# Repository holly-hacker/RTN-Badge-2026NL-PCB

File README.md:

# RTN Badge 2026 (NL edition) PCB

This repo contains the KiCAD schematic for the 2026 RTN Badge (NL edition).

For more info, see the [main repo](https://github.com/holly-hacker/RTN-Badge-2026NL).

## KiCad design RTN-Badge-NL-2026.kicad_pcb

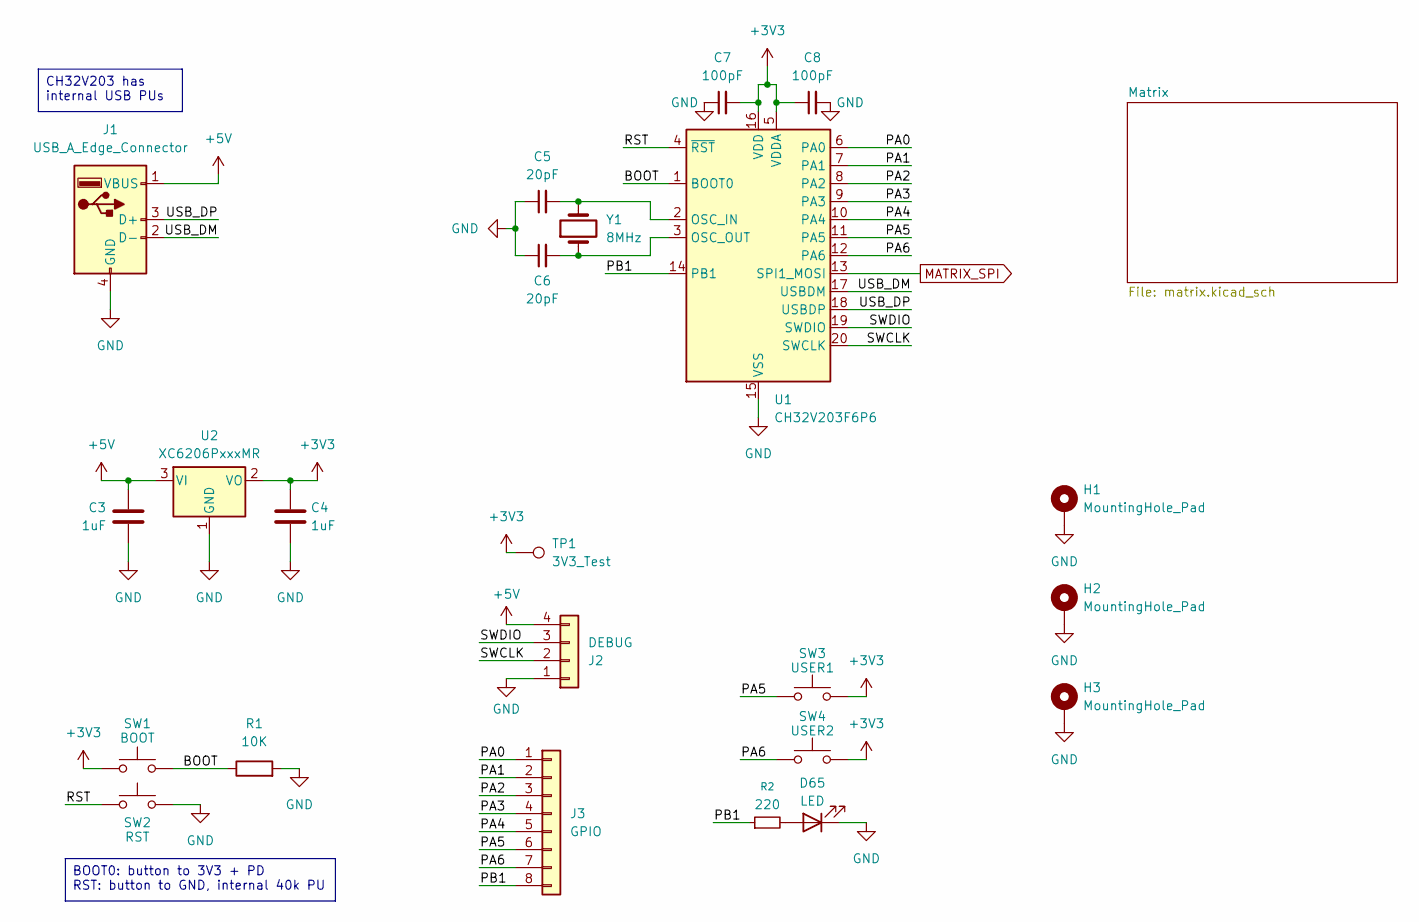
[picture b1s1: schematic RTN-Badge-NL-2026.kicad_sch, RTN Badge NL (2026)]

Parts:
C3, C4: 1uF; C_0603_1608Metric
C5, C6: 20pF; C_0603_1608Metric
C7, C8: 100pF; C_0603_1608Metric
D65: LED; LED_0603_1608Metric
H1, H2, H3: MountingHole_Pad; MountingHole_2.2mm_M2_Pad_Via
J1: USB_A_Edge_Connector; USB_A_PCB_Edge_receptacle
J2: DEBUG; PinSocket_1x04_P2.54mm_Vertical
J3: GPIO; PinSocket_1x08_P2.54mm_Vertical
R1: 10K; R_0603_1608Metric
R2: 220; R_0603_1608Metric
SW1: BOOT; SW_SPST_TS-1088-xR020
SW2: RST; SW_SPST_TS-1088-xR020
SW3: USER1; SW_SPST_TS-1088-xR020
SW4: USER2; SW_SPST_TS-1088-xR020
TP1: 3V3_Test; TestPoint_Pad_D1.0mm
U1: CH32V203F6P6; TSSOP-20_4.4x6.5mm_P0.65mm
U2: XC6206PxxxMR; SOT-23-3
Y1: 8MHz; Crystal_SMD_5032-2Pin_5.0x3.2mm

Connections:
+3V3: C4.1, C7.2, C8.1, SW1.1, SW3.2, SW4.2, TP1.1 (1_1), U1.5 (VDDA), U1.16 (VDD), U2.2 (VO)
+5V: C3.1, J1.1 (VBUS), J2.4, U2.3 (VI); also elsewhere on the board
/BOOT: R1.1, SW1.2, U1.1 (BOOT0)
/PA0: J3.1, U1.6 (PA0)
/PA1: J3.2, U1.7 (PA1)
/PA2: J3.3, U1.8 (PA2)
/PA3: J3.4, U1.9 (PA3)
/PA4: J3.5, U1.10 (PA4)
/PA5: J3.6, SW3.1, U1.11 (PA5)
/PA6: J3.7, SW4.1, U1.12 (PA6)
/PB1: J3.8, R2.1, U1.14 (PB1)
/RST: SW2.1, U1.4 (~RST)
/SWCLK: J2.2, U1.20 (SWCLK)
/SWDIO: J2.3, U1.19 (SWDIO)
/USB_DM: J1.2 (D-), U1.17 (USBDM)
/USB_DP: J1.3 (D+), U1.18 (USBDP)
GND: C3.2, C4.2, C5.1, C6.1, C7.1, C8.2, D65.1 (K), H1.1 (1_1), H2.1 (1_1), H3.1 (1_1), J1.4 (GND), J2.1, R1.2, SW2.2, U1.15 (VSS), U2.1 (GND); also elsewhere on the board
MATRIX_SPI: U1.13 (SPI1_MOSI); also elsewhere on the board
unnamed: D65.2 (A), R2.2
unnamed: C5.2, U1.2 (OSC_IN), Y1.2
unnamed: C6.2, U1.3 (OSC_OUT), Y1.1

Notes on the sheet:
CH32V203 has internal USB PUs
BOOT0: button to 3V3 + PD RST: button to GND, internal 40k PU

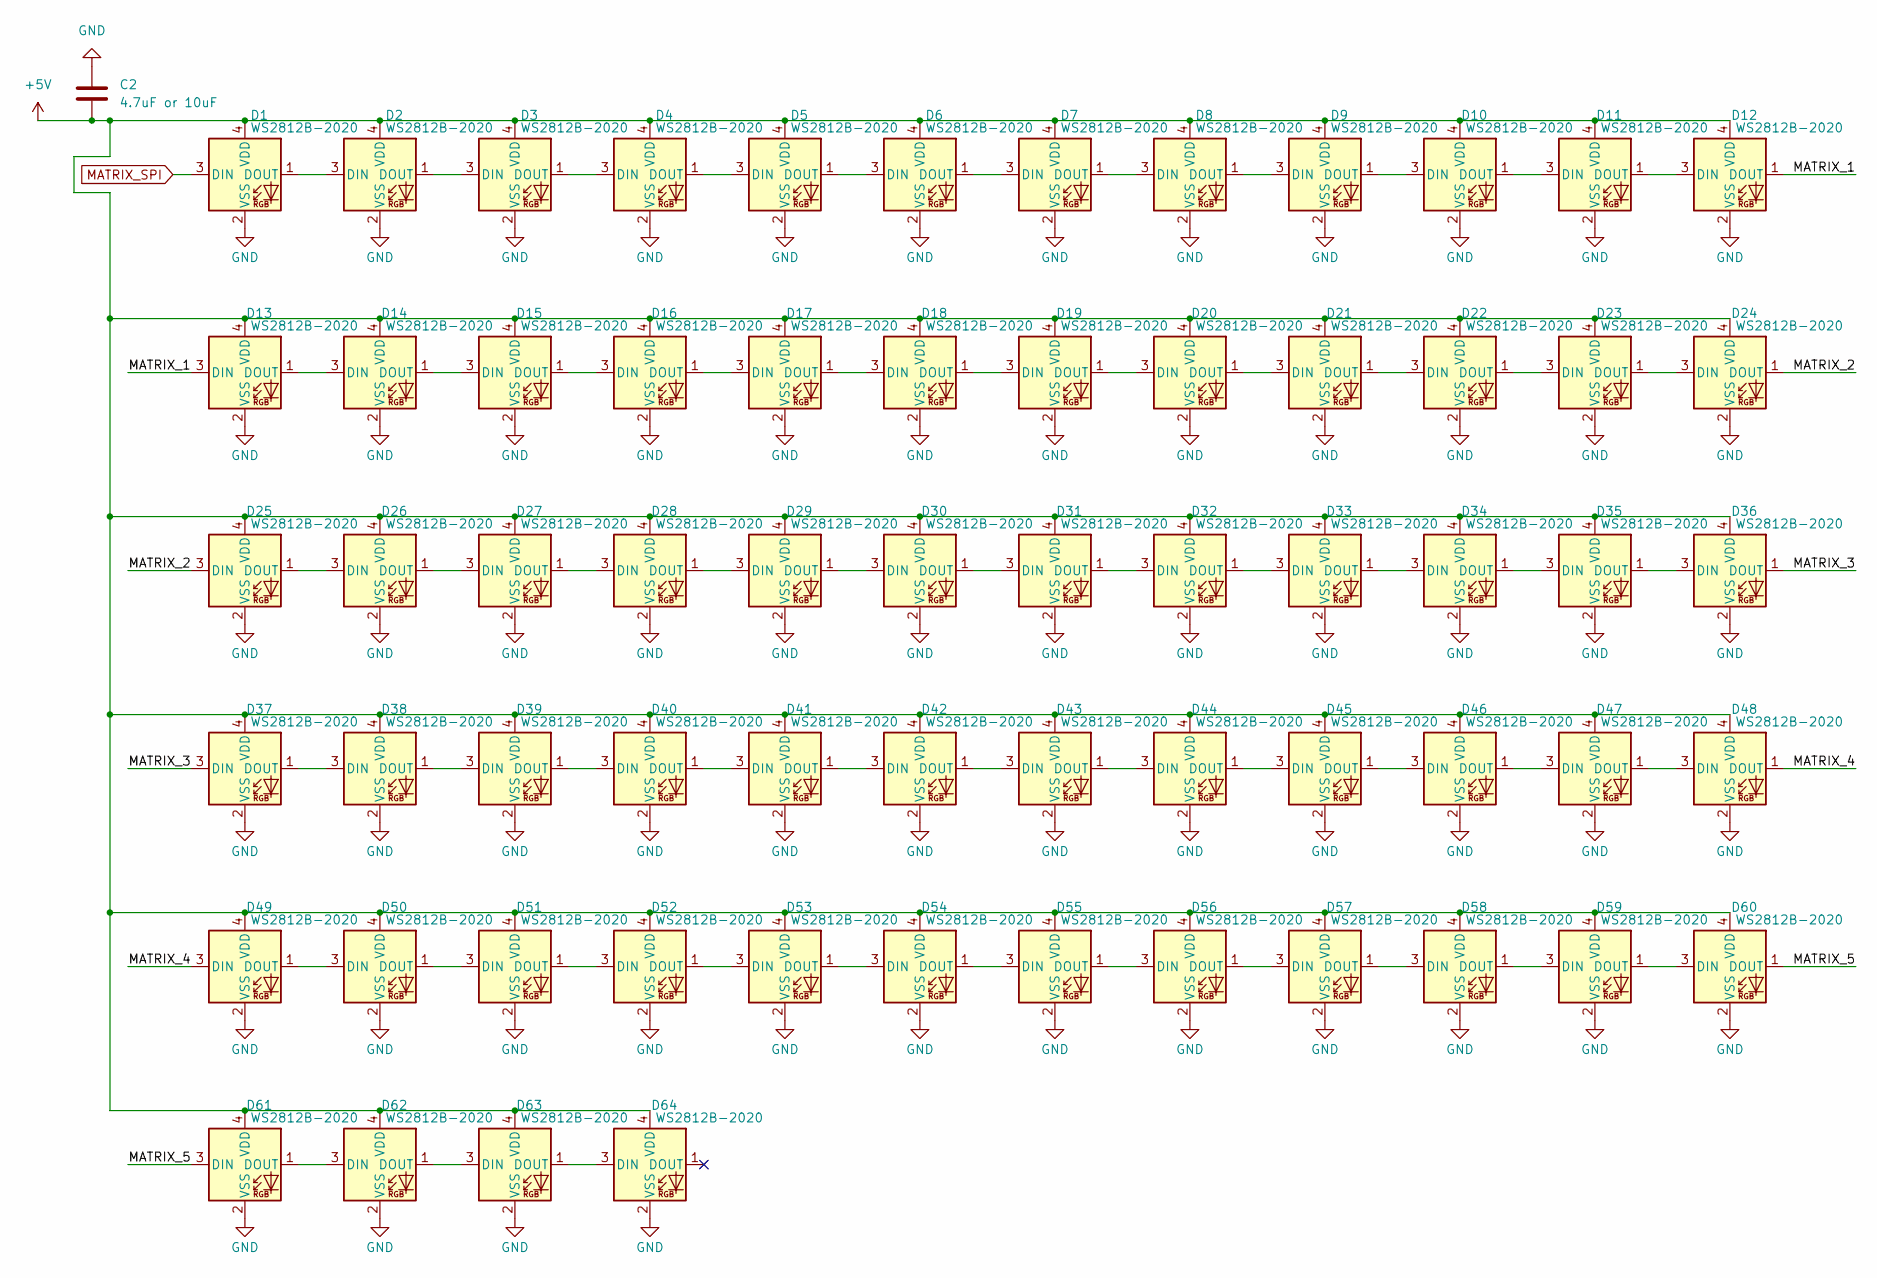
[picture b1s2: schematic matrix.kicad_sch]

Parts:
C2: 4.7uF or 10uF; C_0603_1608Metric
D1, D2, D3, D4, D5, D6, D7, D8, D9, D10, D11, D12, D13, D14, D15, D16, D17, D18, D19, D20, D21, D22, D23, D24, D25, D26, D27, D28, D29, D30, D31, D32, D33, D34, D35, D36, D37, D38, D39, D40, D41, D42, D43, D44, D45, D46, D47, D48, D49, D50, D51, D52, D53, D54, D55, D56, D57, D58, D59, D60, D61, D62, D63, D64: WS2812B-2020; LED_WS2812B-2020_PLCC4_2.0x2.0mm

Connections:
+5V: C2.2, D1.4 (VDD), D2.4 (VDD), D3.4 (VDD), D4.4 (VDD), D5.4 (VDD), D6.4 (VDD), D7.4 (VDD), D8.4 (VDD), D9.4 (VDD), D10.4 (VDD), D11.4 (VDD), D12.4 (VDD), D13.4 (VDD), D14.4 (VDD), D15.4 (VDD), D16.4 (VDD), D17.4 (VDD), D18.4 (VDD), D19.4 (VDD), D20.4 (VDD), D21.4 (VDD), D22.4 (VDD), D23.4 (VDD), D24.4 (VDD), D25.4 (VDD), D26.4 (VDD), D27.4 (VDD), D28.4 (VDD), D29.4 (VDD), D30.4 (VDD), D31.4 (VDD), D32.4 (VDD), D33.4 (VDD), D34.4 (VDD), D35.4 (VDD), D36.4 (VDD), D37.4 (VDD), D38.4 (VDD), D39.4 (VDD), D40.4 (VDD), D41.4 (VDD), D42.4 (VDD), D43.4 (VDD), D44.4 (VDD), D45.4 (VDD), D46.4 (VDD), D47.4 (VDD), D48.4 (VDD), D49.4 (VDD), D50.4 (VDD), D51.4 (VDD), D52.4 (VDD), D53.4 (VDD), D54.4 (VDD), D55.4 (VDD), D56.4 (VDD), D57.4 (VDD), D58.4 (VDD), D59.4 (VDD), D60.4 (VDD), D61.4 (VDD), D62.4 (VDD), D63.4 (VDD), D64.4 (VDD); also elsewhere on the board
/Matrix/MATRIX_1: D12.1 (DOUT), D13.3 (DIN)
/Matrix/MATRIX_2: D24.1 (DOUT), D25.3 (DIN)
/Matrix/MATRIX_3: D36.1 (DOUT), D37.3 (DIN)
/Matrix/MATRIX_4: D48.1 (DOUT), D49.3 (DIN)
/Matrix/MATRIX_5: D60.1 (DOUT), D61.3 (DIN)
GND: C2.1, D1.2 (VSS), D2.2 (VSS), D3.2 (VSS), D4.2 (VSS), D5.2 (VSS), D6.2 (VSS), D7.2 (VSS), D8.2 (VSS), D9.2 (VSS), D10.2 (VSS), D11.2 (VSS), D12.2 (VSS), D13.2 (VSS), D14.2 (VSS), D15.2 (VSS), D16.2 (VSS), D17.2 (VSS), D18.2 (VSS), D19.2 (VSS), D20.2 (VSS), D21.2 (VSS), D22.2 (VSS), D23.2 (VSS), D24.2 (VSS), D25.2 (VSS), D26.2 (VSS), D27.2 (VSS), D28.2 (VSS), D29.2 (VSS), D30.2 (VSS), D31.2 (VSS), D32.2 (VSS), D33.2 (VSS), D34.2 (VSS), D35.2 (VSS), D36.2 (VSS), D37.2 (VSS), D38.2 (VSS), D39.2 (VSS), D40.2 (VSS), D41.2 (VSS), D42.2 (VSS), D43.2 (VSS), D44.2 (VSS), D45.2 (VSS), D46.2 (VSS), D47.2 (VSS), D48.2 (VSS), D49.2 (VSS), D50.2 (VSS), D51.2 (VSS), D52.2 (VSS), D53.2 (VSS), D54.2 (VSS), D55.2 (VSS), D56.2 (VSS), D57.2 (VSS), D58.2 (VSS), D59.2 (VSS), D60.2 (VSS), D61.2 (VSS), D62.2 (VSS), D63.2 (VSS), D64.2 (VSS); also elsewhere on the board
MATRIX_SPI: D1.3 (DIN); also elsewhere on the board
unnamed: D1.1 (DOUT), D2.3 (DIN)
unnamed: D2.1 (DOUT), D3.3 (DIN)
unnamed: D3.1 (DOUT), D4.3 (DIN)
unnamed: D4.1 (DOUT), D5.3 (DIN)
unnamed: D5.1 (DOUT), D6.3 (DIN)
unnamed: D6.1 (DOUT), D7.3 (DIN)
unnamed: D7.1 (DOUT), D8.3 (DIN)
unnamed: D8.1 (DOUT), D9.3 (DIN)
unnamed: D9.1 (DOUT), D10.3 (DIN)
unnamed: D10.1 (DOUT), D11.3 (DIN)
unnamed: D11.1 (DOUT), D12.3 (DIN)
unnamed: D13.1 (DOUT), D14.3 (DIN)
unnamed: D14.1 (DOUT), D15.3 (DIN)
unnamed: D15.1 (DOUT), D16.3 (DIN)
unnamed: D16.1 (DOUT), D17.3 (DIN)
unnamed: D17.1 (DOUT), D18.3 (DIN)
unnamed: D18.1 (DOUT), D19.3 (DIN)
unnamed: D19.1 (DOUT), D20.3 (DIN)
unnamed: D20.1 (DOUT), D21.3 (DIN)
unnamed: D21.1 (DOUT), D22.3 (DIN)
unnamed: D22.1 (DOUT), D23.3 (DIN)
unnamed: D23.1 (DOUT), D24.3 (DIN)
unnamed: D25.1 (DOUT), D26.3 (DIN)
unnamed: D26.1 (DOUT), D27.3 (DIN)
unnamed: D27.1 (DOUT), D28.3 (DIN)
unnamed: D28.1 (DOUT), D29.3 (DIN)
unnamed: D29.1 (DOUT), D30.3 (DIN)
unnamed: D30.1 (DOUT), D31.3 (DIN)
unnamed: D31.1 (DOUT), D32.3 (DIN)
unnamed: D32.1 (DOUT), D33.3 (DIN)
unnamed: D33.1 (DOUT), D34.3 (DIN)
unnamed: D34.1 (DOUT), D35.3 (DIN)
unnamed: D35.1 (DOUT), D36.3 (DIN)
unnamed: D37.1 (DOUT), D38.3 (DIN)
unnamed: D38.1 (DOUT), D39.3 (DIN)
unnamed: D39.1 (DOUT), D40.3 (DIN)
unnamed: D40.1 (DOUT), D41.3 (DIN)
unnamed: D41.1 (DOUT), D42.3 (DIN)
unnamed: D42.1 (DOUT), D43.3 (DIN)
unnamed: D43.1 (DOUT), D44.3 (DIN)
unnamed: D44.1 (DOUT), D45.3 (DIN)
unnamed: D45.1 (DOUT), D46.3 (DIN)
unnamed: D46.1 (DOUT), D47.3 (DIN)
unnamed: D47.1 (DOUT), D48.3 (DIN)
unnamed: D49.1 (DOUT), D50.3 (DIN)
unnamed: D50.1 (DOUT), D51.3 (DIN)
unnamed: D51.1 (DOUT), D52.3 (DIN)
unnamed: D52.1 (DOUT), D53.3 (DIN)
unnamed: D53.1 (DOUT), D54.3 (DIN)
unnamed: D54.1 (DOUT), D55.3 (DIN)
unnamed: D55.1 (DOUT), D56.3 (DIN)
unnamed: D56.1 (DOUT), D57.3 (DIN)
unnamed: D57.1 (DOUT), D58.3 (DIN)
unnamed: D58.1 (DOUT), D59.3 (DIN)
unnamed: D59.1 (DOUT), D60.3 (DIN)
unnamed: D61.1 (DOUT), D62.3 (DIN)
unnamed: D62.1 (DOUT), D63.3 (DIN)
unnamed: D63.1 (DOUT), D64.3 (DIN)

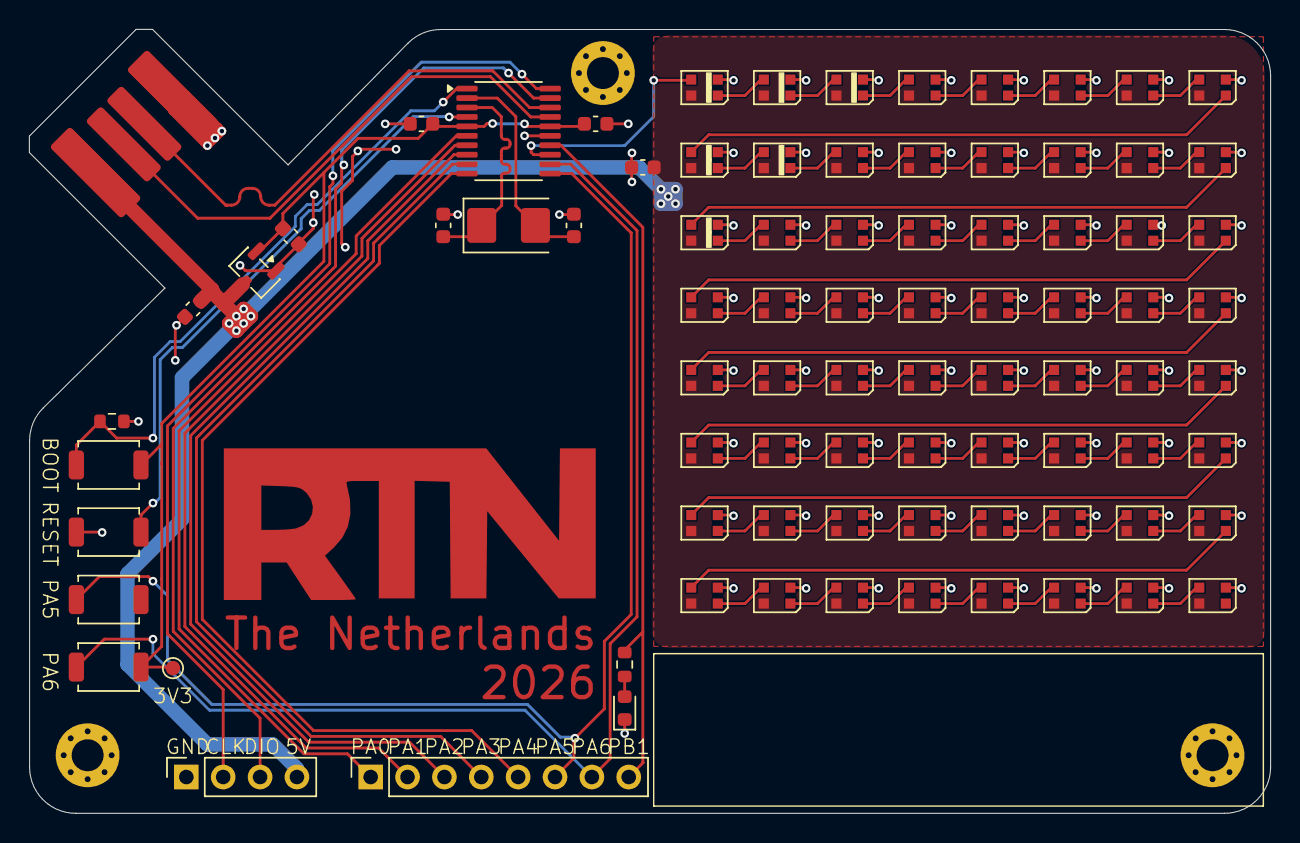
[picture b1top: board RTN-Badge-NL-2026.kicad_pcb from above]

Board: 2 copper layers, 85.5 x 54.0 mm, 88 parts (0 on the bottom side), 84 nets.

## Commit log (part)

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2026-06-17 Init gitignore
2026-06-28 Create initial design
2026-06-28 Adjust PCB to use components available in JLCPCB's product library
